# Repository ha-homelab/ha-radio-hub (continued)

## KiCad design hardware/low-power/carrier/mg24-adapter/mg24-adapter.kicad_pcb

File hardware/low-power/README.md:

# Low-power LP-P0: prototype hardware contract

<!-- MC2-CURRENT-DESIGN -->
> **Current build: [MC2 — three external antennas](../../docs/external-antennas.md).** This page retains an earlier design or evaluation for reference. Its board images, pin maps, enclosure fit and alternative BOMs are not the current MC2 build.

This is a separate design with **one S3 host and one Ethernet interface**, three dedicated radio controllers H2/MG24/ZAC93, and CC1101. Assembly, firmware for the individual radio modules and hardware testing are required. No board has been fabricated or tested, and there is no verified “3 W” result.
The [ready-module carrier](carrier/) and [integrated board](integrated/) are
separate engineering revisions; use their own verification reports and connector maps.

The current calculation gives scenarios of **2.03 / 2.82 / 4.92 W incremental AC power**. These are not measurements or a confidence interval. **3 W AC is a testable target**, not a guaranteed specification. Detailed assumptions, current reserves and calculation boundaries are in [power-budget.json](power-budget.json); the earlier architectures are compared separately in [energy-comparison.json](energy-comparison.json).

## Files and validation

- [BOM](bom.json): exact main models, quantities, `bench`/`carrier`/`both` stages and primary sources. Do not combine alternatives for different stages into a single order.
- [Pinmap](pinmap.json) and [wiring CSV](wiring.csv): 26 unique S3 GPIOs, three native UARTs and two SPI buses. The CSV defines signals; a GPIO number is not a header contact number.
- [Visual connection atlas](visual/README.md): offline interactive pin-to-pin guide, part identification sketches and printable connection sheets, with physical-pad evidence and unverified header positions distinguished.
- [Manufacturing and sales](../../docs/manufacturing.md): first articles, batch sizes, fabrication services and all three delivery formats.
- The [combined firmware](../../firmware/low-power/hub.yaml) uses the same GPIOs. Build status and software limitations are in [firmware/low-power](../../firmware/low-power/).
- [Enclosure mockup](../../mechanical/low-power/): 160×100 mm carrier reservation, 190×145×45 mm shell. The EvalPoE/DevKit development boards are not claimed to fit this enclosure.

Run from the repository root: `python3 hardware/low-power/validate.py`. This checks contracts and arithmetic, not electrical operation.

## Two assembly stages

**Bench:** external active IEEE 802.3af/at PSE → Ethernet cable → **Silvertel EvalPoE fitted with Ag97005-FL**. EvalPoE `DATA OUT` → short RJ45 patch cable → **WIZ850io**. EvalPoE isolated 5 V output → fused distribution → LD2450 and **Pololu D24V22F3**. The shared 3.3 V buck output powers S3, H2, MGM240P, ZAC93, CC1101, SC16 and BME680. There is no internal switch; one external cable supplies power.

EvalPoE compatibility with Ag97000-FL is explicitly stated on the [manufacturer's page](https://silvertel.com/ag97000/), although the PDF manual lists older models. Specify **Ag97005-FL** when ordering rather than assuming the module is included with an empty EvalPoE. Check bridge-bypass and output-filter settings against the revision of the [EvalPoE manual](https://silvertel.com/images/Eval-Board-User-Guides/POE-Eval-Board-User-Manual.pdf): the FL uses its built-in bridges, bypasses the external bridge, uses class 0 and keeps the nominal untrimmed output. Measure 5 V and polarity before connecting logic.

**Ready-module carrier (LP-C0):** distributes isolated 5 V and regulated 3.3 V,
provides a local SC16/clock/reset circuit and keyed harnesses to the controller,
radios and sensors. Its [MG24 daughterboard](carrier/mg24-adapter/) mounts the
exact MGM240PA22VNA3 and provides UART, BOOT and SWD service access.
The external EvalPoE, buck, WIZ850io and radio boards still
need separate mounting. A bare carrier does not include those modules.

**Integrated board (LP-I0):** places the bare S3/H2/MGM240P modules, W5500,
PoE magjack, Ag97005-FL, buck and support circuits on a separate PCB. ZAC93,
CC1101, radar and the external BME680 remain cable-connected. It needs its own
larger enclosure and physical bring-up; the earlier concept case is not a fit claim.

**WIZ850io does not expose PoE center taps on its SPI headers. Do not connect
Ag97005-FL inputs to those headers.** LP-C0 retains the external isolated front
end; LP-I0 uses its own specified PoE-capable magjack. A successful CAD check
is not validation of PoE isolation, Ethernet performance or radio coexistence.
Until the boards pass bring-up, EvalPoE on the bench remains the assembly path.

## Power and calculation

The selected [Ag97005-FL](https://silvertel.com/images/datasheets/Ag97000-Datasheet-low-cost-isolated-12W-Power-over-Ethernet-PoE-module-solution.pdf) is the 5 V/9 W version, 1.8 A nominal. The generic “12 W” describes the family, not this SKU. Class 0 is retained for startup/peaks; an average of 3 W AC alone does not justify selecting class 1. Use the recommended 100 µF + 100 nF + 10 µF output capacitors, accounting for parts already installed on EvalPoE. The main output-capacitance range is 47–470 µF; check additional capacitance and buck startup with an oscilloscope.

The peak **design reserve**, adding simultaneous loads, is 1.025 A at 3.3 V and 0.25 A directly at 5 V. At 85% buck efficiency and 0.15 W distribution loss, this is **5.38 W at the PD output**. It is not a guaranteed maximum for the actual modules. [D24V22F3](https://www.pololu.com/product/2857) is advertised as 2.6 A typical under specified conditions; this assembly needs a separate **1.5 A test with 5 V input** and thermal verification. Do not apply a 24 V input rating at 5 V without a curve/test. A 1.5 A slow-blow fuse on the secondary 5 V branch is an initial candidate; select the final I²t after startup testing and checking wire gauge.

Average-consumption model: `P5 = P3.3 / ηbuck + Pradar + Pwiring`, then `PAC = P5 / ηPD / ηcable / ηPSE`. The ηPD input/output boundaries are the PoE module pins; built-in bridges are already included. Low-voltage wiring is counted once. The 81.5% value is the selected FL's **peak typical** datasheet efficiency, not a guaranteed efficiency at 1.9 W. The model uses 68/76/81.5%; the two lower values are assumptions pending measurement. Add the fixed consumption of a new dedicated PSE separately; the already-running shared HA server and baseline network-infrastructure consumption are excluded.

The minimum load for maintaining PoE MPS is 70 mA at 5 V. Continuous LD2450 operation normally supplies this load, but startup and fault states must be checked; no parallel resistor for waste heat is added in advance. Required network/BLE/radar functions must remain active: disabling them does not qualify as reaching 3 W. The W5500 firmware forces 10 Mbps half-duplex; the budget deliberately retains the conservative 100 Mbps estimate without subtracting expected savings. Link stability and actual power have not yet been measured.

## S3, UARTs and the actual DevKit

The target module is **ESP32-S3-WROOM-1-N16R8**. GPIO26–37 are excluded because of flash/PSRAM, 19/20 are reserved for native USB, and 0/3/45/46 are excluded as strapping pins. GPIO38 is free. UART0 belongs to LD2450, UART1 to the MG24 TCP bridge with RTS/CTS, and UART2 to H2 OTBR. These UART numbers do not determine physical GPIOs: the GPIO matrix is used. There is no fourth native UART, so ZAC93 connects through SC16IS752.

Existing DevKits require **physical** changes before connection:

1. The S3 development board's USB–UART TX must not drive GPIO44, which receives H2 TX. Check/isolate the USB–UART connections to 43/44 and the effect of auto-reset against the actual board schematic. Selecting native USB in YAML does not disconnect these traces.
2. Similarly, on the H2 DevKit, check and isolate USB–UART TX from GPIO23, which will receive S3 data. Do not join two push-pull outputs.
3. GPIO48 must be free of the RGB LED; the official DevKitC-1 v1.1 has its LED on 38, while the earlier version uses 48. An “N16R8” label does not identify the board revision.
4. External 3.3 V and USB/5 V must not power different regulators in parallel. Disconnect the shared supply and peripherals for initial flashing; on a running bench setup, use a verified USB data-only/isolated-VBUS path. Check for back-powering and loading of an unpowered controller through UART.

The [official DevKit guide](https://docs.espressif.com/projects/esp-idf/en/v5.1.2/esp32s3/hw-reference/esp32s3/user-guide-devkitc-1.html) and [S3 datasheet](https://www.espressif.com/sites/default/files/documentation/esp32-s3-wroom-1_wroom-1u_datasheet_en.pdf) define these constraints. An unverified clone cannot be treated as a drop-in board for this pinout.

## H2 and MG24

**ESP32-H2-MINI-1-H4S**, 4 MB, is a dedicated Thread RCP, not another IP host. S3 TX43 → H2 GPIO23 RX, H2 GPIO24 TX → S3 RX44. S3 GPIO47 controls EN and GPIO48 controls BOOT/GPIO9; both outputs are open-drain, with HIGH meaning the line is released through an external pull-up. EN: 10 kΩ to 3.3 V + 1 µF to GND; BOOT: 10 kΩ to 3.3 V. Also pull H2 GPIO8 up to 3.3 V through 10 kΩ: download boot requires GPIO8=1, GPIO9=0. Hold GPIO25 low with 10 kΩ to GND; do not change eFuses. Keep EN/BOOT/GND service test points accessible. [H2 datasheet](https://www.espressif.com/sites/default/files/documentation/esp32-h2-mini-1_mini-1u_datasheet_en.pdf).

**MGM240PA22VNA3** is the selected +10 dBm MG24 variant with a built-in antenna. It requires a custom Ember NCP image with UART 115200, 8N1 and hardware RTS/CTS matching this contract: S3 TX17 → PA05/pad12 RX; PA06/pad13 TX → S3 RX18; S3 RTS16 → PB01/pad5 CTS; PB00/pad6 RTS → S3 CTS21. An [NCP and UART-XMODEM bootloader have been built](../../firmware/low-power/mg24/) for this assignment using Simplicity SDK 2025.6.3 / Zigbee 8.2.3 / EZSP 18. Generation, compilation, CRC and image checks passed; module flashing, UART/CTS, pairing and radio-network operation have not yet been tested. Factory and SLZB images are not claimed to be interchangeable.

To enter the built bootloader, expose **PA00/pad7 BOOT** with 10 kΩ to 3.3 V and a separate service jumper to GND; hold it LOW during reset. This uses no S3 GPIO. For SWD, expose PA01/pad8 SWCLK, PA02/pad9 SWDIO, RESETn/pad31, GND and 3.3 V VTref. RESETn has an internal pull-up to DVDD: only pull it to GND and release it; **do not add an external pull-up to 3.3 V**. Connect power to VDD/pad15 and all GND pins according to the [MGM240P datasheet](https://www.silabs.com/documents/public/data-sheets/mgm240p-datasheet.pdf). Verify the service-connector pinout against the selected programmer; USB-UART does not replace SWD for initial programming of a blank module.

## SC16IS752 and ZAC93

The selected part is **SC16IS752IPW,128, TSSOP28**. SPI is shared with CC1101, with separate CS pins GPIO41 and 15. IRQ pin15 → S3 GPIO42, with **1 kΩ to 3.3 V**, according to [NXP rev9.1](https://www.nxp.com/docs/en/data-sheet/SC16IS752_SC16IS762.pdf). I2C/SPI pin9 and unused SDA pin14 → GND. Supply pin8=3.3 V, pin22=GND. The current driver uses SPI mode 0 at 4 MHz; the SC16IS752 limit is 4 MHz, not the SC16IS762's 15 MHz.

Channel A: TXA/pin3 → ZAC93 header pin8 RX; ZAC93 pin10 TX → RXA/pin4. ZAC93 pin1=3.3 V, pin6/9=GND; do not connect other contacts without checking the revision. Hardware flow control is disabled; CTSA/pin2 and CTSB/pin16 → GND; RXB/pin24 is pulled up to 3.3 V through 10 kΩ; RTSA/RTSB/TXB outputs remain unconnected. The eight unused GPIOs have separate 100 kΩ resistors to GND to prevent floating inputs without shorting a future output.

Use an **ABLS-3.6864MHZ-B2-T** crystal between XTAL1/pin6 and XTAL2/pin7; prescaler 1 and divisor 2 give 115200 baud. Initial 22/33 pF C0G load capacitors come from the NXP example and require frequency/startup checks with the actual 18 pF crystal and stray capacitance. Initially keep the SPI harness no longer than 5 cm and check edges/noise with an oscilloscope; adjust driver speed and repeat testing if needed. **The firmware setting `crystal_frequency: 3686400` is mandatory.** A typical off-the-shelf 14.7456 MHz breakout is not interchangeable without configuration/driver changes.

RESET/pin5 receives the open-drain output of **TPS3808G33DBVR**, with 10 kΩ to 3.3 V; VDD/SENSE=3.3 V, CT unconnected (20 ms), and MR may use its internal pull-up or a button to GND. Install 100 nF at VDD and 1 nF at SENSE. [TI datasheet](https://www.ti.com/lit/ds/symlink/tps3808.pdf). SC16 power starts alongside the S3; software reset does not replace slow-ramp/brownout testing.

A 64-byte FIFO fills in about 5.56 ms of continuous data at 115200 8N1. The handler must service IRQ before the remaining FIFO headroom runs out; a 2048-byte software queue cannot compensate for late hardware-FIFO reads. Stress-test alongside RF TX, BLE, Ethernet and Thread. Loss/overrun must not silently turn into valid Z-Wave messages.

## RF, sensors, antennas and enclosure

CC1101: shared SPI7/8/6, CS15, GDO0→GPIO4 open-drain with 4.7 kΩ to 3.3 V, GDO2→GPIO5. This is a two-signal RF design; boards without accessible GDO2 need a separate solution. Preserve the existing RF contract/encodings when connecting to the new host. Check the clone's physical contacts against its markings, not an arbitrary photo.

LD2450 receives 5 V directly from the PD, with UART TX→S3 GPIO40 and RX←GPIO39 and common secondary GND. BME680 VIN receives 3.3 V, SDA1/SCL2, 100 kHz, address 0x77. Use the stock Adafruit pull-ups; keep the external pod away from heat and initially limit I²C to 10–20 cm. Adding sensors requires capacitance/edge margin; a free address does not imply GPIO/power headroom. BME680 gas resistance is not a direct CO₂ measurement.

Retain the stock antennas: S3 PCB, H2 PCB, built-in MGM240P, regional ZAC93 and the existing 433 MHz CC1101 antenna. Do not substitute 2.4/5.8 GHz antennas for 433 MHz. Place antennas along the carrier edges, away from metal, buck/PoE circuitry and cable bundles; apply each module's datasheet keep-out rather than a single general rule. Simultaneous BLE/Thread/Zigbee operation at 2.4 GHz requires loss/latency checks and channel selection. Individual radio certifications do not certify the combined enclosure.

The radar looks through a 1.2 mm nonmetallic wall; radome geometry and the absence of conductive fillers matter. ZAC93 limits ambient temperature around it to 0…40 °C; the S3 N16R8 has a 65 °C limit, which does not justify heating ZAC93 above 40 °C. Measure air temperature near the modules separately from buck surface temperature. The low-power drawings retain **unmeasured** envelopes for the existing ZAC93/CC1101, wires and connectors.

## Before releasing a hardware revision

1. Check actual modules/connectors, DevKit UART isolation, GDO2, GPIO48 and the 3.3 V supply. Do not connect unisolated interfaces with two active drivers.
2. Assemble on the bench with EvalPoE; check rails, MPS, cold start, load transients and thermal performance. Record AC and DC separately.
3. Flash H2 and MG24, check UART/CTS and SC16 without RF load, then exercise all functions together, including long runs and recovery from power/Ethernet loss.
4. Review the selected PCB revision and its verification report before first-article fabrication. Resolve electrical, isolation, return-path, RF keep-out and mechanical findings, then run DFM and bench validation. The earlier enclosure mockup is not proof of fit for either complete assembly.

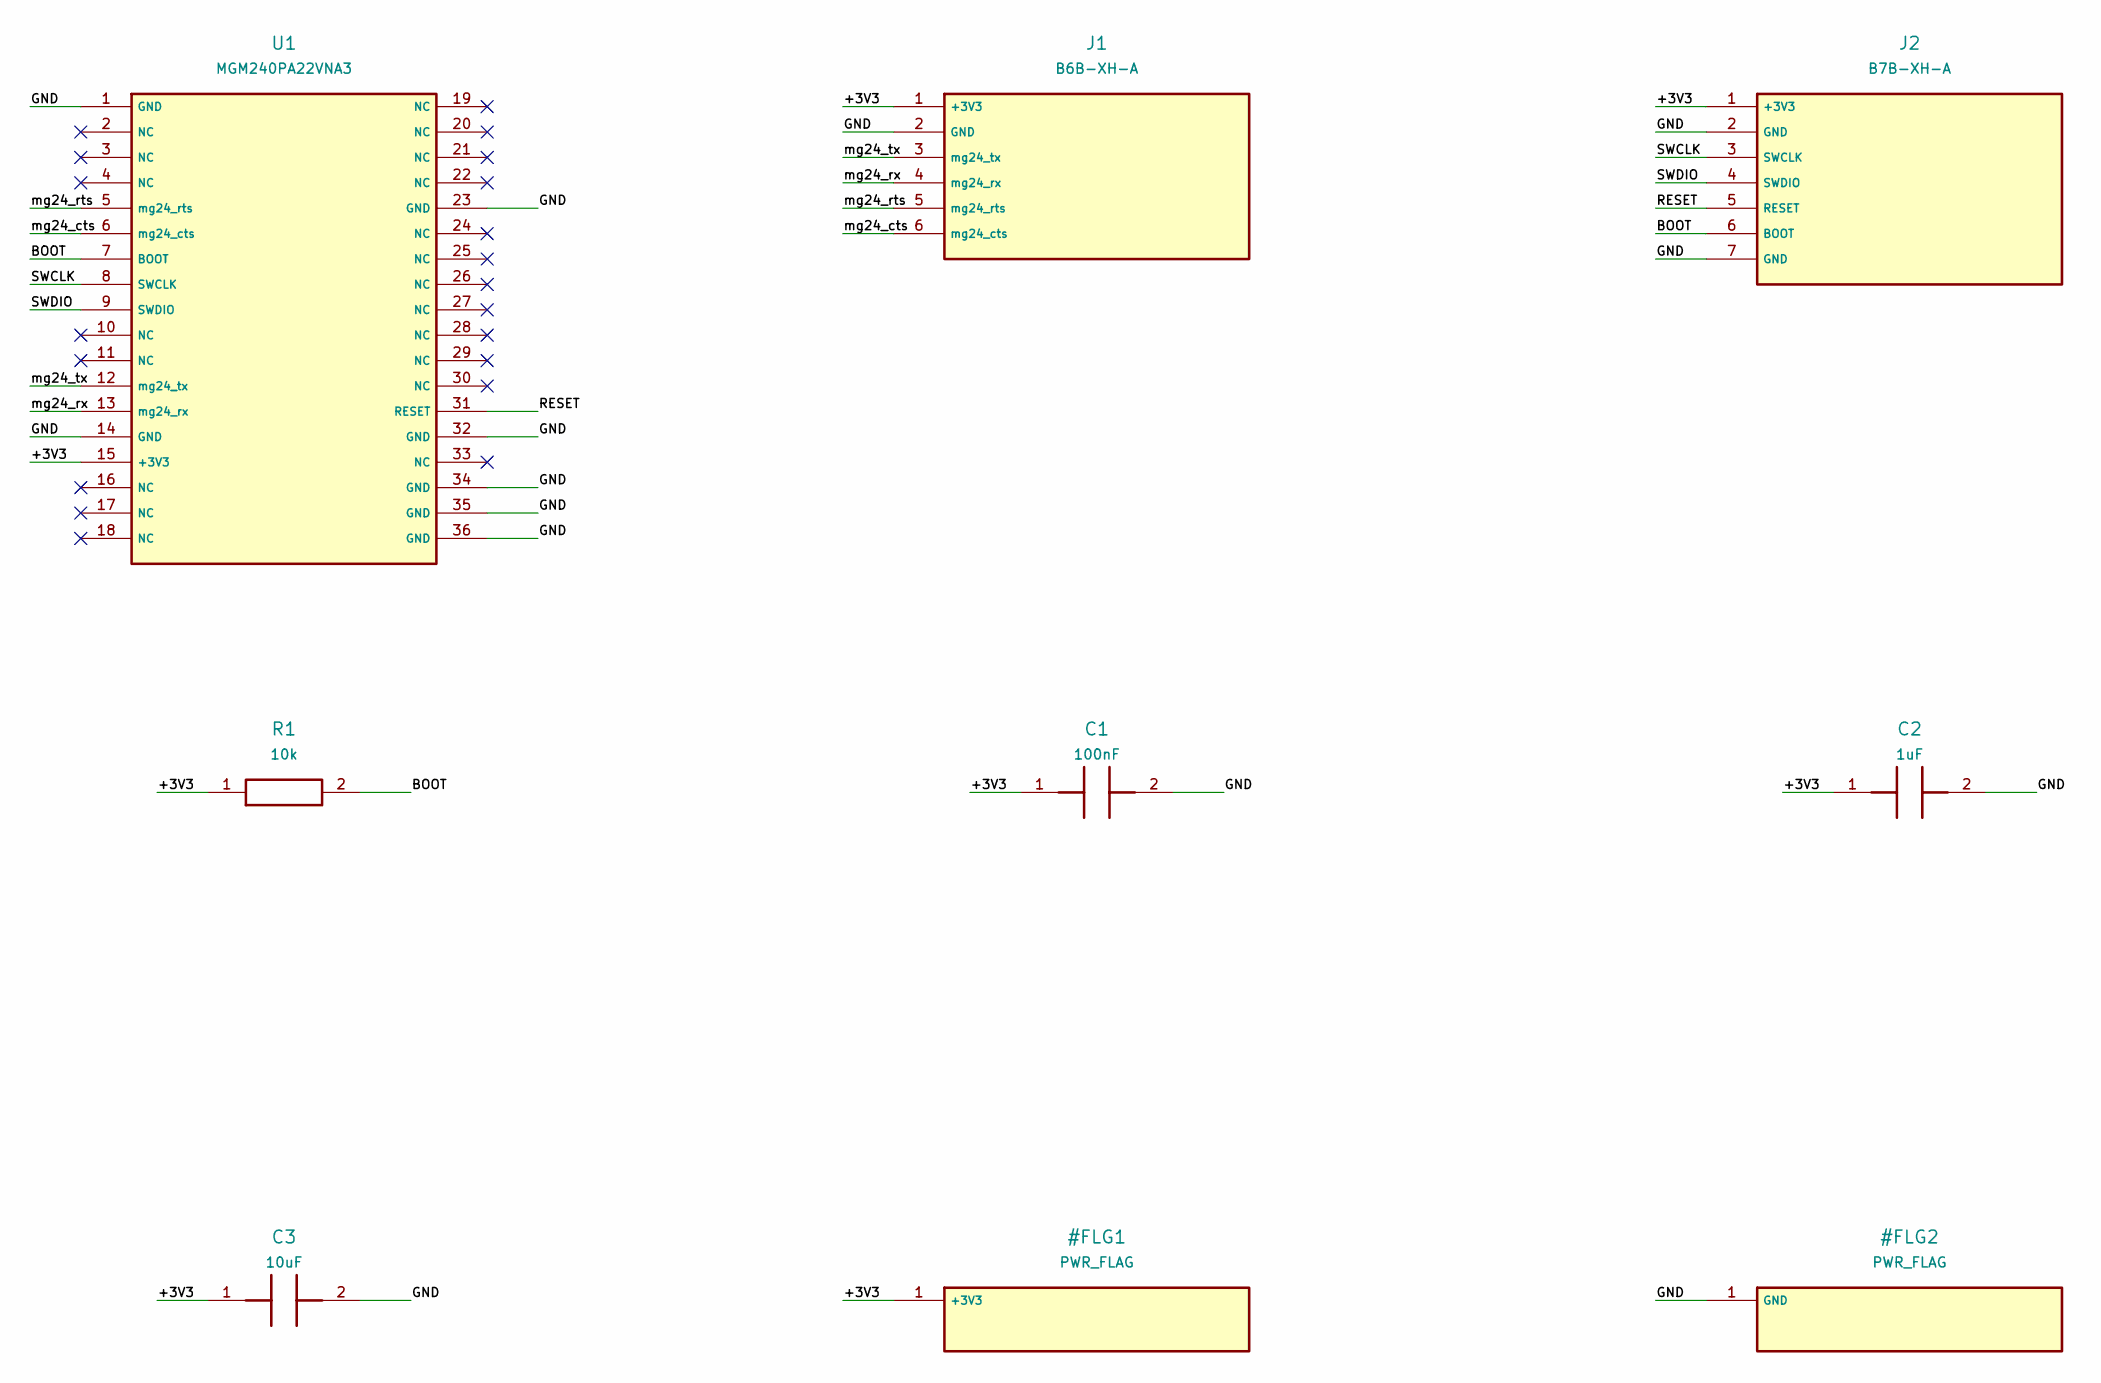
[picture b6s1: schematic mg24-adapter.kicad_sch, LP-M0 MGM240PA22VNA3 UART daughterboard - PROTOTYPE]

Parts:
C1: 100nF; C_0805_2012Metric
C2: 1uF; C_0805_2012Metric
C3: 10uF; C_1206_3216Metric
J1: B6B-XH-A; JST_XH_B6B-XH-A_1x06_P2.50mm_Vertical
J2: B7B-XH-A; JST_XH_B7B-XH-A_1x07_P2.50mm_Vertical
R1: 10k; R_0805_2012Metric
U1: MGM240PA22VNA3; MGM240P

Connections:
/+3V3: C1.1, C2.1, C3.1, J1.1 (+3V3), J2.1 (+3V3), R1.1, U1.15 (+3V3)
/BOOT: J2.6 (BOOT), R1.2, U1.7 (BOOT)
/GND: C1.2, C2.2, C3.2, J1.2 (GND), J2.2 (GND), J2.7 (GND), U1.1 (GND), U1.14 (GND), U1.23 (GND), U1.32 (GND), U1.34 (GND), U1.35 (GND), U1.36 (GND)
/RESET: J2.5 (RESET), U1.31 (RESET)
/SWCLK: J2.3 (SWCLK), U1.8 (SWCLK)
/SWDIO: J2.4 (SWDIO), U1.9 (SWDIO)
/mg24_cts: J1.6 (mg24_cts), U1.6 (mg24_cts)
/mg24_rts: J1.5 (mg24_rts), U1.5 (mg24_rts)
/mg24_rx: J1.4 (mg24_rx), U1.13 (mg24_rx)
/mg24_tx: J1.3 (mg24_tx), U1.12 (mg24_tx)

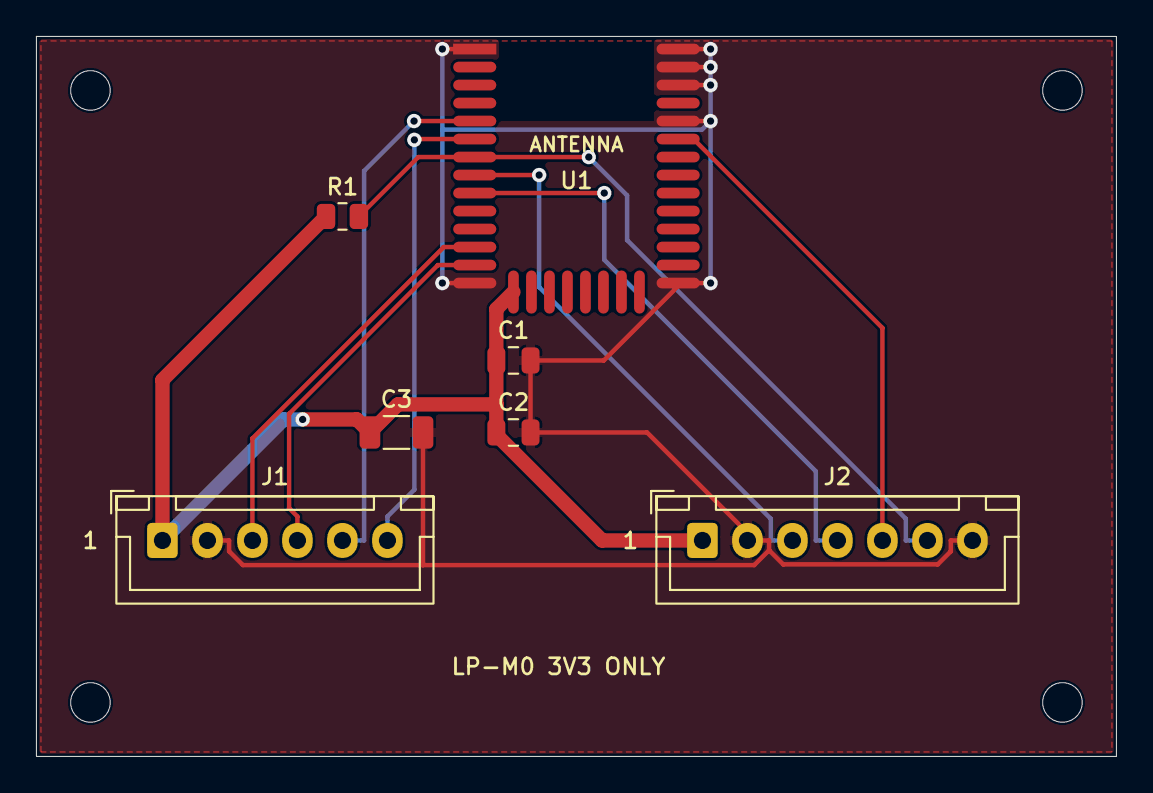
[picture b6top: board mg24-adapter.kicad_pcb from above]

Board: 2 copper layers, 60.0 x 40.0 mm, 11 parts (0 on the bottom side), 10 nets.

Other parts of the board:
H1, H2, H3, H4: M2 NPTH

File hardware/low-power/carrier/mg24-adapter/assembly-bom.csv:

Reference,Quantity,Manufacturer part / value,Footprint,Note,Source
U1,1,MGM240PA22VNA3,Carrier:MGM240P,Exact PA22VNA3 firmware target; all GND pads direct to plane; RFOUT33 intentionally NC,https://www.silabs.com/documents/public/data-sheets/mgm240p-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
J1,1,B6B-XH-A,Carrier:JST_XH_B6B-XH-A_1x06_P2.50mm_Vertical,To carrier J6,https://www.jst-mfg.com/product/pdf/eng/eXH.pdf
J2,1,B7B-XH-A,Carrier:JST_XH_B7B-XH-A_1x07_P2.50mm_Vertical,SWD / reset / boot service,https://www.jst-mfg.com/product/pdf/eng/eXH.pdf
R1,1,10k,Carrier:R_0805_2012Metric,"1%, 0.125W, 0805",
C1,1,100nF,Carrier:C_0805_2012Metric,"10V X7R, 0805, close to VDD15",
C2,1,1uF,Carrier:C_0805_2012Metric,"10V X7R, 0805",
C3,1,10uF,Carrier:C_1206_3216Metric,"10V X7R, 1206; account for DC bias",

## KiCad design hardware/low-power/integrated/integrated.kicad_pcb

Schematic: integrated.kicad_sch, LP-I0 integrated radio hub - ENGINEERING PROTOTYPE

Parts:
C1: 22pF; C_0805_2012Metric
C2: 33pF; C_0805_2012Metric
C3, C6, C9, C13, C15, C17, C18, C19, C20, C21, C22, C23, C24, C25, C27, C42: 100nF; C_0805_2012Metric
C4, C7, C10, C26, C28, C43: 10uF; C_1206_3216Metric
C5, C8, C12: 1uF; C_0805_2012Metric
C11: 100nF; C_0603_1608Metric
C14: 1nF; C_0805_2012Metric
C16, C39, C40, C41: 22uF; C_1206_3216Metric
C29, C36: 10nF; C_0805_2012Metric
C30: 4.7uF; C_0805_2012Metric
C31, C32: 18pF; C_0805_2012Metric
C33: 22nF; C_0805_2012Metric
C34, C35: 6.8nF; C_0805_2012Metric
C37, C38: 10nF 100V; C_1206_3216Metric
C50: 1nF 2kV; C_Disc_D7.5mm_W5.0mm_P7.50mm
D1, D2: SMBJ58CA; D_SMB
F1: 044901.5MR; Littelfuse_449
FB1: BLM21PG121SN1D; L_0805_2012Metric
J1: 0813-1X1T-57-F; Bel_0813_1X1T_57_F
J2: TYPE-C-31-M-12; USB_C_Receptacle_HRO_TYPE-C-31-M-12
J3: B8B-XH-A; JST_XH_B8B-XH-A_1x08_P2.50mm_Vertical
J4: B5B-XH-A; JST_XH_B5B-XH-A_1x05_P2.50mm_Vertical
J5: B4B-XH-A; JST_XH_B4B-XH-A_1x04_P2.50mm_Vertical
J6: BM04B-SRSS-TB; JST_SH_BM04B-SRSS-TB_1x04-1MP_P1.00mm_Vertical
J7, J8: B6B-XH-A; JST_XH_B6B-XH-A_1x06_P2.50mm_Vertical
R1: 1k; R_0805_2012Metric
R2, R3, R4, R6, R7, R8, R9, R10, R11, R12, R13, R14, R15, R16: 10k; R_0805_2012Metric
R5: 4.7k; R_0805_2012Metric
R17, R18: 5.1k; R_0805_2012Metric
R19, R20: 22; R_0805_2012Metric
R21, R22, R23, R24, R25, R26, R27, R28: 100k; R_0805_2012Metric
R29: 12.4k; R_0805_2012Metric
R30: 1M; R_0805_2012Metric
R31, R32, R34, R35: 49.9; R_0805_2012Metric
R33: 10; R_0805_2012Metric
SW1, SW2, SW3, SW4: SW_PUSH; SW_SPST_TL3342
U1: ESP32-S3-WROOM-1-N16R8; ESP32-S3-WROOM-1
U2: ESP32-H2-MINI-1-H4S; ESP32-H2-MINI-1
U3: MGM240PA22VNA3; MGM240P
U4: W5500; LQFP-48_7x7mm_P0.5mm
U5: NXP SC16IS752IPW,128 / TSSOP28; TSSOP-28_4.4x9.7mm_P0.65mm
U6: TI TPS3808G33DBVR / SOT-23-6; SOT-23-6
U7: Ag97005-FL; Ag97000_FL
U8: D24V22F3
U9: USBLC6-2SC6; SOT-23-6
Y1: ABLS-3.6864MHZ-B2-T; Crystal_SMD_HC49-SD
Y2: ABM8-25.000MHZ-B2-T; Crystal_SMD_3225-4Pin_3.2x2.5mm

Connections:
3v3: C3.1 (3v3), C4.1 (3v3), C6.1 (3v3), C7.1 (3v3), C9.1 (3v3), C10.1 (3v3), C11.1 (3v3), C12.1 (3v3), C13.1 (3v3), C14.1 (3v3), C16.1 (3v3), C17.1 (3v3), C18.1 (3v3), C27.1 (3v3), C28.1 (3v3), FB1.1 (3v3), J3.1 (3v3), J4.1 (3v3), J6.2 (3v3), J7.1 (3v3), J8.1 (3v3), R1.2 (3v3), R2.2 (3v3), R3.2 (3v3), R4.2 (3v3), R5.2 (3v3), R6.2 (3v3), R7.2 (3v3), R8.2 (3v3), R9.2 (3v3), R11.2 (3v3), R12.2 (3v3), R13.2 (3v3), R14.2 (3v3), R15.2 (3v3), R16.2 (3v3), U1.2 (3v3), U2.3 (3v3), U3.15 (3v3), U4.28 (3v3), U5.8 (3v3), U6.5 (3v3), U6.6 (3v3), U8.VOUT (3v3)
3v3_analog: C20.1 (3v3_analog), C21.1 (3v3_analog), C22.1 (3v3_analog), C23.1 (3v3_analog), C24.1 (3v3_analog), C25.1 (3v3_analog), C26.1 (3v3_analog), FB1.2 (3v3_analog), R31.2 (3v3_analog), R32.2 (3v3_analog), R33.2 (3v3_analog), U4.4 (3v3_analog), U4.8 (3v3_analog), U4.11 (3v3_analog), U4.15 (3v3_analog), U4.17 (3v3_analog), U4.21 (3v3_analog)
5v_fused: C19.1 (5v_fused), F1.2 (5v_fused), J5.1 (5v_fused), U8.VIN (5v_fused)
5v_pd: C39.1 (5v_pd), C40.1 (5v_pd), C41.1 (5v_pd), C42.1 (5v_pd), C43.1 (5v_pd), F1.1 (5v_pd), U7.8 (5v_pd)
POE_12: C37.1 (POE_12), D1.1 (POE_12), J1.5 (POE_12), U7.1 (POE_12)
POE_36: C37.2 (POE_36), D1.2 (POE_36), J1.10 (POE_36), U7.2 (POE_36)
POE_45: C38.1 (POE_45), D2.1 (POE_45), J1.6 (POE_45), U7.3 (POE_45)
POE_78: C38.2 (POE_78), D2.2 (POE_78), J1.11 (POE_78), U7.4 (POE_78)
bme680_scl: J6.4 (bme680_scl), U1.38 (bme680_scl)
bme680_sda: J6.3 (bme680_sda), U1.39 (bme680_sda)
cc1101_cs: J3.6 (cc1101_cs), R6.1 (cc1101_cs), U1.8 (cc1101_cs)
cc1101_gdo0_tx: J3.7 (cc1101_gdo0_tx), R5.1 (cc1101_gdo0_tx), U1.4 (cc1101_gdo0_tx)
cc1101_gdo2_rx: J3.8 (cc1101_gdo2_rx), U1.5 (cc1101_gdo2_rx)
chassis: C50.1 (chassis), J1.S1 (chassis), J1.S2 (chassis)
eth_1v2: C29.1 (eth_1v2), U4.22 (eth_1v2)
eth_exres: R29.1 (eth_exres), U4.10 (eth_exres)
eth_pmode: R16.1 (eth_pmode), U4.43 (eth_pmode), U4.44 (eth_pmode), U4.45 (eth_pmode)
eth_rxn: C35.1 (eth_rxn), R35.1 (eth_rxn), U4.5 (eth_rxn)
eth_rxp: C34.1 (eth_rxp), R34.1 (eth_rxp), U4.6 (eth_rxp)
eth_rxterm: C36.1 (eth_rxterm), R34.2 (eth_rxterm), R35.2 (eth_rxterm)
eth_tocap: C30.1 (eth_tocap), U4.20 (eth_tocap)
eth_txn: J1.9 (eth_txn), R32.1 (eth_txn), U4.1 (eth_txn)
eth_txp: J1.2 (eth_txp), R31.1 (eth_txp), U4.2 (eth_txp)
eth_xi: C31.1 (eth_xi), R30.1 (eth_xi), U4.30 (eth_xi), Y2.1 (eth_xi)
eth_xo: C32.1 (eth_xo), R30.2 (eth_xo), U4.31 (eth_xo), Y2.3 (eth_xo)
gnd: C1.2 (gnd), C2.2 (gnd), C3.2 (gnd), C4.2 (gnd), C5.2 (gnd), C6.2 (gnd), C7.2 (gnd), C8.2 (gnd), C9.2 (gnd), C10.2 (gnd), C11.2 (gnd), C12.2 (gnd), C13.2 (gnd), C14.2 (gnd), C15.2 (gnd), C16.2 (gnd), C17.2 (gnd), C18.2 (gnd), C19.2 (gnd), C20.2 (gnd), C21.2 (gnd), C22.2 (gnd), C23.2 (gnd), C24.2 (gnd), C25.2 (gnd), C26.2 (gnd), C27.2 (gnd), C28.2 (gnd), C29.2 (gnd), C30.2 (gnd), C31.2 (gnd), C32.2 (gnd), C33.2 (gnd), C36.2 (gnd), C39.2 (gnd), C40.2 (gnd), C41.2 (gnd), C42.2 (gnd), C43.2 (gnd), C50.2 (gnd), J2.A1 (gnd), J2.A12 (gnd), J2.B1 (gnd), J2.B12 (gnd), J2.SH (gnd), J3.2 (gnd), J4.2 (gnd), J4.5 (gnd), J5.2 (gnd), J6.1 (gnd), J7.2 (gnd), J8.2 (gnd), R10.2 (gnd), R17.2 (gnd), R18.2 (gnd), R21.2 (gnd), R22.2 (gnd), R23.2 (gnd), R24.2 (gnd), R25.2 (gnd), R26.2 (gnd), R27.2 (gnd), R28.2 (gnd), R29.2 (gnd), SW1.2 (gnd), SW2.2 (gnd), SW3.2 (gnd), SW4.2 (gnd), U1.1 (gnd), U1.40 (gnd), U1.41 (gnd), U2.1 (gnd), U2.2 (gnd), U2.11 (gnd), U2.14 (gnd), U2.36 (gnd), U2.37 (gnd), U2.38 (gnd), U2.39 (gnd), U2.40 (gnd), U2.41 (gnd), U2.42 (gnd), U2.43 (gnd), U2.44 (gnd), U2.45 (gnd), U2.46 (gnd), U2.47 (gnd), U2.48 (gnd), U2.49 (gnd), U2.50 (gnd), U2.51 (gnd), U2.52 (gnd), U2.53 (gnd), U3.1 (gnd), U3.14 (gnd), U3.23 (gnd), U3.32 (gnd), U3.34 (gnd), U3.35 (gnd), U3.36 (gnd), U4.3 (gnd), U4.9 (gnd), U4.14 (gnd), U4.16 (gnd), U4.19 (gnd), U4.23 (gnd), U4.29 (gnd), U4.48 (gnd), U5.2 (gnd), U5.9 (gnd), U5.14 (gnd), U5.16 (gnd), U5.22 (gnd), U6.2 (gnd), U7.7 (gnd), U8.GND (gnd), U8.GND2 (gnd), U9.2 (gnd), Y2.2 (gnd), Y2.4 (gnd)
h2_boot: J8.6 (h2_boot), R8.1 (h2_boot), U1.25 (h2_boot), U2.23 (h2_boot)
h2_gpio8: R9.1 (h2_gpio8), U2.22 (h2_gpio8)
h2_gpio25: R10.1 (h2_gpio25), U2.25 (h2_gpio25)
h2_reset: C8.1 (h2_reset), J8.5 (h2_reset), R7.1 (h2_reset), U1.24 (h2_reset), U2.8 (h2_reset)
h2_rx: J8.3 (h2_rx), U1.36 (h2_rx), U2.31 (h2_rx)
h2_tx: J8.4 (h2_tx), U1.37 (h2_tx), U2.30 (h2_tx)
ld2450_rx: J5.3 (ld2450_rx), U1.33 (ld2450_rx)
ld2450_tx: J5.4 (ld2450_tx), U1.32 (ld2450_tx)
mag_ct: C33.1 (mag_ct), J1.7 (mag_ct), R33.1 (mag_ct)
mag_rxn: C35.2 (mag_rxn), J1.8 (mag_rxn)
mag_rxp: C34.2 (mag_rxp), J1.1 (mag_rxp)
mg24_boot: J7.6 (mg24_boot), R11.1 (mg24_boot), SW4.1 (mg24_boot), U3.7 (mg24_boot)
mg24_cts: U1.23 (mg24_cts), U3.6 (mg24_cts)
mg24_reset: J7.5 (mg24_reset), SW3.1 (mg24_reset), U3.31 (mg24_reset)
mg24_rts: U1.9 (mg24_rts), U3.5 (mg24_rts)
mg24_rx: U1.11 (mg24_rx), U3.13 (mg24_rx)
mg24_swclk: J7.3 (mg24_swclk), U3.8 (mg24_swclk)
mg24_swdio: J7.4 (mg24_swdio), U3.9 (mg24_swdio)
mg24_tx: U1.10 (mg24_tx), U3.12 (mg24_tx)
s3_boot: R13.1 (s3_boot), SW2.1 (s3_boot), U1.27 (s3_boot)
s3_en: C5.1 (s3_en), R12.1 (s3_en), SW1.1 (s3_en), U1.3 (s3_en)
sc16_cs: R3.1 (sc16_cs), U1.34 (sc16_cs), U5.10 (sc16_cs)
sc16_gpio0: R21.1 (sc16_gpio0), U5.18 (sc16_gpio0)
sc16_gpio1: R22.1 (sc16_gpio1), U5.19 (sc16_gpio1)
sc16_gpio2: R23.1 (sc16_gpio2), U5.20 (sc16_gpio2)
sc16_gpio3: R24.1 (sc16_gpio3), U5.21 (sc16_gpio3)
sc16_gpio4: R25.1 (sc16_gpio4), U5.25 (sc16_gpio4)
sc16_gpio5: R26.1 (sc16_gpio5), U5.26 (sc16_gpio5)
sc16_gpio6: R27.1 (sc16_gpio6), U5.27 (sc16_gpio6)
sc16_gpio7: R28.1 (sc16_gpio7), U5.28 (sc16_gpio7)
sc16_irq: R1.1 (sc16_irq), U1.35 (sc16_irq), U5.15 (sc16_irq)
sc16_reset: R2.1 (sc16_reset), U5.5 (sc16_reset), U6.1 (sc16_reset)
sc16_rxb: R4.1 (sc16_rxb), U5.24 (sc16_rxb)
sc16_xtal1: C1.1 (sc16_xtal1), U5.6 (sc16_xtal1), Y1.1 (sc16_xtal1)
sc16_xtal2: C2.1 (sc16_xtal2), U5.7 (sc16_xtal2), Y1.2 (sc16_xtal2)
shared_spi_miso: J3.5 (shared_spi_miso), U1.6 (shared_spi_miso), U5.12 (shared_spi_miso)
shared_spi_mosi: J3.4 (shared_spi_mosi), U1.12 (shared_spi_mosi), U5.11 (shared_spi_mosi)
shared_spi_sclk: J3.3 (shared_spi_sclk), U1.7 (shared_spi_sclk), U5.13 (shared_spi_sclk)
usb_cc1: J2.A5 (usb_cc1), R17.1 (usb_cc1)
usb_cc2: J2.B5 (usb_cc2), R18.1 (usb_cc2)
usb_dm: R19.2 (usb_dm), U1.13 (usb_dm)
usb_dm_port: J2.A7 (usb_dm_port), J2.B7 (usb_dm_port), R19.1 (usb_dm_port), U9.1 (usb_dm_port), U9.6 (usb_dm_port)
usb_dp: R20.2 (usb_dp), U1.14 (usb_dp)
usb_dp_port: J2.A6 (usb_dp_port), J2.B6 (usb_dp_port), R20.1 (usb_dp_port), U9.3 (usb_dp_port), U9.4 (usb_dp_port)
usb_vbus: C15.1 (usb_vbus), J2.A4 (usb_vbus), J2.A9 (usb_vbus), J2.B4 (usb_vbus), J2.B9 (usb_vbus), U9.5 (usb_vbus)
w5500_cs: R14.1 (w5500_cs), U1.22 (w5500_cs), U4.32 (w5500_cs)
w5500_irq: U1.18 (w5500_irq), U4.36 (w5500_irq)
w5500_miso: U1.20 (w5500_miso), U4.34 (w5500_miso)
w5500_mosi: U1.19 (w5500_mosi), U4.35 (w5500_mosi)
w5500_reset: R15.1 (w5500_reset), U1.17 (w5500_reset), U4.37 (w5500_reset)
w5500_sclk: U1.21 (w5500_sclk), U4.33 (w5500_sclk)
zwave_rx: J4.4 (zwave_rx), U5.4 (zwave_rx)
zwave_tx: J4.3 (zwave_tx), U5.3 (zwave_tx)

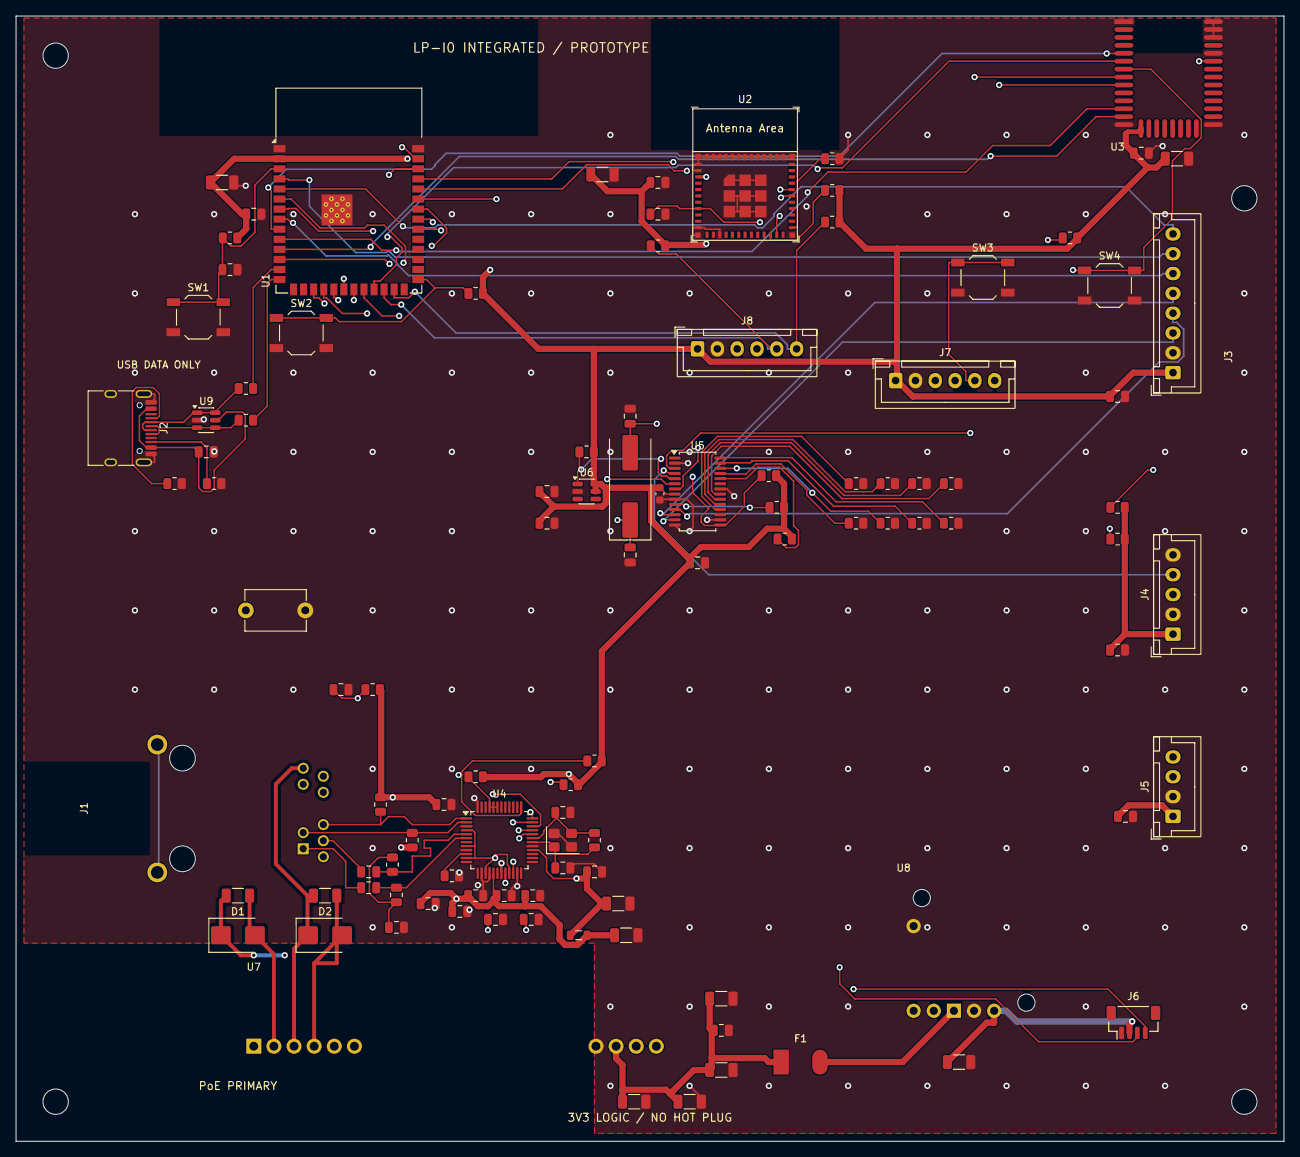
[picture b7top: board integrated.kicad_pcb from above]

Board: 4 copper layers, 160.0 x 142.0 mm, 110 parts (0 on the bottom side), 79 nets.

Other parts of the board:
H1, H2, H3, H4: M3 NPTH; MountingHole_3.2mm_M3

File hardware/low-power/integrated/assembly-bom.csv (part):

Reference,Quantity,Manufacturer part / value,Footprint,Note,Source
U1,1,ESP32-S3-WROOM-1-N16R8,Hub:ESP32-S3-WROOM-1,"Module pad numbers, not development-board header positions.","{'url': 'https://www.espressif.com/sites/default/files/documentation/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, 'revision': '1.8', 'section': 'Table 3-1, pages 11-12', 'checked_date': '2026-10-17'}"
U2,1,ESP32-H2-MINI-1-H4S,Hub:ESP32-H2-MINI-1,"Module pad numbers, not development-board header positions.","{'url': 'https://www.espressif.com/sites/default/files/documentation/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, 'revision': '1.6', 'section': 'Table 3, page 10', 'checked_date': '2026-10-17'}"
U3,1,MGM240PA22VNA3,Hub:MGM240P,"Module pad numbers, not development-board header positions.","{'url': 'https://www.silabs.com/documents/public/data-sheets/mgm240p-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, 'revision': '1.4', 'section': '6.1, Table 6.1', 'checked_date': '2026-10-17', 'method': 'Manufacturer PDF indexed pin table; direct PDF download unavailable during this review.'}"
U5,1,"NXP SC16IS752IPW,128 / TSSOP28",Hub:TSSOP-28_4.4x9.7mm_P0.65mm,"Module pad numbers, not development-board header positions.","{'url': 'https://www.nxp.com/docs/en/data-sheet/SC16IS752_SC16IS762.pdf', 'revision': '9.1', 'section': 'Table 2, TSSOP28 column only', 'checked_date': '2026-10-17'}"
U6,1,TI TPS3808G33DBVR / SOT-23-6,Hub:SOT-23-6,"Module pad numbers, not development-board header positions.",
U7,1,Ag97005-FL,Hub:Ag97000_FL,Bare isolated PoE module installed on this PCB; not the separate EvalPoE bench board.,"{'url': 'https://silvertel.com/images/datasheets/Ag97000-Datasheet-lo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, 'revision': '2.0', 'section': 'Table 3, Ag97000-FL, page 5', 'checked_date': '2026-10-17'}"
U8,1,D24V22F3,Hub:D24V22F3,Only regulator feeding 3V3. 1.5A at 5V input bench gate; soldered headers.,https://www.pololu.com/file/0J1031/d24v22fx-step-down-voltag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
U4,1,W5500,Hub:LQFP-48_7x7mm_P0.5mm,25MHz crystal; common-CT magnetics with RX AC coupling; hardware PMODE111; firmware selects10M.,https://docs.wiznet.io/img/products/w5500/w5500_sch_v110_use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
J1,1,0813-1X1T-57-F,Hub:Bel_0813_1X1T_57_F,"PoE-capable magjack. PHY-side common CT. Four cable-side power taps, internal bridge in U7.",https://www.belfuse.com/media/drawings/products/magjack%20IC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
J3,1,B8B-XH-A,Hub:JST_XH_B8B-XH-A_1x08_P2.50mm_Vertical,CC1101 remote RF module,https://www.jst-mfg.com/product/pdf/eng/eXH.pdf
J4,1,B5B-XH-A,Hub:JST_XH_B5B-XH-A_1x05_P2.50mm_Vertical,ZAC93 remote module,https://www.jst-mfg.com/product/pdf/eng/eXH.pdf
J5,1,B4B-XH-A,Hub:JST_XH_B4B-XH-A_1x04_P2.50mm_Vertical,LD2450 remote radar,https://www.jst-mfg.com/product/pdf/eng/eXH.pdf
J6,1,BM04B-SRSS-TB,Hub:JST_SH_BM04B-SRSS-TB_1x04-1MP_P1.00mm_Vertical,Standard QT order; breakout pullups only; short external ambient sensor cable.,https://www.jst-mfg.com/product/pdf/eng/eSH.pdf
J7,1,B6B-XH-A,Hub:JST_XH_B6B-XH-A_1x06_P2.50mm_Vertical,MG24 service SWD/boot,https://www.jst-mfg.com/product/pdf/eng/eXH.pdf
J8,1,B6B-XH-A,Hub:JST_XH_B6B-XH-A_1x06_P2.50mm_Vertical,H2 service UART/boot,https://www.jst-mfg.com/product/pdf/eng/eXH.pdf
J2,1,TYPE-C-31-M-12,Hub:USB_C_Receptacle_HRO_TYPE-C-31-M-12,Self-powered USB service only. VBUS feeds ESD reference; never tied to PoE5V.,https://www.hroelec.com/UploadFiles/2017/04/TYPE-C-31-M-12.pdf
U9,1,USBLC6-2SC6,Hub:SOT-23-6,Low-capacitance ESD near USB; VBUS not board supply.,https://www.st.com/resource/en/datasheet/usblc6-2.pdf
Y1,1,ABLS-3.6864MHZ-B2-T,Hub:Crystal_SMD_HC49-SD,18pF load; verify measured frequency and drive.,"{'url': 'https://www.nxp.com/docs/en/data-sheet/SC16IS752_SC16IS762.pdf', 'revision': '9.1', 'section': 'Table 2, TSSOP28 column only', 'checked_date': '2026-10-17'}"
C1,1,22pF,Hub:C_0805_2012Metric,"C0G,50V",
C2,1,33pF,Hub:C_0805_2012Metric,"C0G,50V",
R1,1,1k,Hub:R_0805_2012Metric,"1%,0805,0.125W",
R2,1,10k,Hub:R_0805_2012Metric,"1%,0805,0.125W",
R3,1,10k,Hub:R_0805_2012Metric,"1%,0805,0.125W",
R4,1,10k,Hub:R_0805_2012Metric,"1%,0805,0.125W",
R5,1,4.7k,Hub:R_0805_2012Metric,"1%,0805,0.125W",
R6,1,10k,Hub:R_0805_2012Metric,"1%,0805,0.125W",
R7,1,10k,Hub:R_0805_2012Metric,"1%,0805,0.125W",
R8,1,10k,Hub:R_0805_2012Metric,"1%,0805,0.125W",
R9,1,10k,Hub:R_0805_2012Metric,"1%,0805,0.125W",
R10,1,10k,Hub:R_0805_2012Metric,"1%,0805,0.125W",
R11,1,10k,Hub:R_0805_2012Metric,"1%,0805,0.125W",
R12,1,10k,Hub:R_0805_2012Metric,"1%,0805,0.125W",
R13,1,10k,Hub:R_0805_2012Metric,"1%,0805,0.125W",
R14,1,10k,Hub:R_0805_2012Metric,"1%,0805,0.125W",
R15,1,10k,Hub:R_0805_2012Metric,"1%,0805,0.125W",
R16,1,10k,Hub:R_0805_2012Metric,"1%,0805,0.125W",
R17,1,5.1k,Hub:R_0805_2012Metric,"1%,0805,0.125W",
R18,1,5.1k,Hub:R_0805_2012Metric,"1%,0805,0.125W",
R19,1,22,Hub:R_0805_2012Metric,"1%,0805,0.125W",
R20,1,22,Hub:R_0805_2012Metric,"1%,0805,0.125W",
R21,1,100k,Hub:R_0805_2012Metric,"1%,0805,0.125W",
R22,1,100k,Hub:R_0805_2012Metric,"1%,0805,0.125W",
R23,1,100k,Hub:R_0805_2012Metric,"1%,0805,0.125W",
R24,1,100k,Hub:R_0805_2012Metric,"1%,0805,0.125W",
R25,1,100k,Hub:R_0805_2012Metric,"1%,0805,0.125W",
R26,1,100k,Hub:R_0805_2012Metric,"1%,0805,0.125W",
R27,1,100k,Hub:R_0805_2012Metric,"1%,0805,0.125W",
R28,1,100k,Hub:R_0805_2012Metric,"1%,0805,0.125W",
C3,1,100nF,Hub:C_0805_2012Metric,"X7R,16V; evaluate DC-bias effective capacitance",
C4,1,10uF,Hub:C_1206_3216Metric,"X7R,16V; evaluate DC-bias effective capacitance",
C5,1,1uF,Hub:C_0805_2012Metric,"X7R,16V; evaluate DC-bias effective capacitance",
C6,1,100nF,Hub:C_0805_2012Metric,"X7R,16V; evaluate DC-bias effective capacitance",
C7,1,10uF,Hub:C_1206_3216Metric,"X7R,16V; evaluate DC-bias effective capacitance",
C8,1,1uF,Hub:C_0805_2012Metric,"X7R,16V; evaluate DC-bias effective capacitance",
C9,1,100nF,Hub:C_0805_2012Metric,"X7R,16V; evaluate DC-bias effective capacitance",
C10,1,10uF,Hub:C_1206_3216Metric,"X7R,16V; evaluate DC-bias effective capacitance",
C11,1,100nF,Hub:C_0603_1608Metric,"X7R,16V; evaluate DC-bias effective capacitance",
C12,1,1uF,Hub:C_0805_2012Metric,"X7R,16V; evaluate DC-bias effective capacitance",
C13,1,100nF,Hub:C_0805_2012Metric,"X7R,16V; evaluate DC-bias effective capacitance",
C14,1,1nF,Hub:C_0805_2012Metric,"X7R,16V; evaluate DC-bias effective capacitance",
C15,1,100nF,Hub:C_0805_2012Metric,"X7R,16V; evaluate DC-bias effective capacitance",
C16,1,22uF,Hub:C_1206_3216Metric,"X7R,16V; evaluate DC-bias effective capacitance",
C17,1,100nF,Hub:C_0805_2012Metric,"X7R,16V; evaluate DC-bias effective capacitance",
C18,1,100nF,Hub:C_0805_2012Metric,"X7R,16V; evaluate DC-bias effective capacitance",
C19,1,100nF,Hub:C_0805_2012Metric,"X7R,16V; evaluate DC-bias effective capacitance",
FB1,1,BLM21PG121SN1D,Hub:L_0805_2012Metric,"120ohm at100MHz, low DCR ferrite; local analog supply filter.",
C20,1,100nF,Hub:C_0805_2012Metric,"X7R,16V; evaluate DC-bias effective capacitance",
C21,1,100nF,Hub:C_0805_2012Metric,"X7R,16V; evaluate DC-bias effective capacitance",
C22,1,100nF,Hub:C_0805_2012Metric,"X7R,16V; evaluate DC-bias effective capacitance",
C23,1,100nF,Hub:C_0805_2012Metric,"X7R,16V; evaluate DC-bias effective capacitance",
C24,1,100nF,Hub:C_0805_2012Metric,"X7R,16V; evaluate DC-bias effective capacitance",
C25,1,100nF,Hub:C_0805_2012Metric,"X7R,16V; evaluate DC-bias effective capacitance",
C26,1,10uF,Hub:C_1206_3216Metric,"X7R,16V; evaluate DC-bias effective capacitance",
C27,1,100nF,Hub:C_0805_2012Metric,"X7R,16V; evaluate DC-bias effective capacitance",
C28,1,10uF,Hub:C_1206_3216Metric,"X7R,16V; evaluate DC-bias effective capacitance",
R29,1,12.4k,Hub:R_0805_2012Metric,"1%,0805,0.125W",
C29,1,10nF,Hub:C_0805_2012Metric,"X7R,16V; evaluate DC-bias effective capacitance",
C30,1,4.7uF,Hub:C_0805_2012Metric,"X7R,16V; evaluate DC-bias effective capacitance",
Y2,1,ABM8-25.000MHZ-B2-T,Hub:Crystal_SMD_3225-4Pin_3.2x2.5mm,"25MHz,18pF load,<=50ppm total; verify crystal ordering specification.",
R30,1,1M,Hub:R_0805_2012Metric,"1%,0805,0.125W",
C31,1,18pF,Hub:C_0805_2012Metric,"C0G,50V",
C32,1,18pF,Hub:C_0805_2012Metric,"C0G,50V",
R31,1,49.9,Hub:R_0805_2012Metric,"1%,0805,0.125W",
R32,1,49.9,Hub:R_0805_2012Metric,"1%,0805,0.125W",
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
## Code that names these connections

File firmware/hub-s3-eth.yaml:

# Waveshare ESP32-S3-ETH-M, ESP32-S3R8 / 16MB flash.
# No camera, microSD card, or expansion board may be fitted: their pins are reused.
substitutions:
  node_name: ha-radio-hub-sensors
  friendly_name: HA Radio Hub Sensors
  bme680_address: "0x77"

esphome:
  name: ${node_name}
  friendly_name: ${friendly_name}
  min_version: 2026.10.2
  compile_process_limit: 2

esp32:
  board: esp32-s3-devkitc-1
  flash_size: 16MB
  framework:
    type: esp-idf

# Official ESPHome Waveshare ESP32-S3-ETH pin mapping.
ethernet:
  type: W5500
  clk_pin: GPIO13
  mosi_pin: GPIO11
  miso_pin: GPIO12
  cs_pin: GPIO14
  interrupt_pin: GPIO10
  reset_pin: GPIO9
  clock_speed: 20MHz

logger:
  level: INFO
  baud_rate: 0

api:
  encryption:
    key: !secret api_encryption_key
  reboot_timeout: 0s

ota:
  - platform: esphome
    password: !secret ota_password

esp32_ble_tracker:

bluetooth_proxy:
  active: true
  connection_slots: 3

uart:
  - id: zwave_uart
    tx_pin: GPIO17
    rx_pin: GPIO18
    baud_rate: 115200
    rx_buffer_size: 1024
    parity: NONE
    stop_bits: 1
  - id: radar_uart
    tx_pin: GPIO4
    rx_pin: GPIO5
    baud_rate: 256000
    rx_buffer_size: 1024
    parity: NONE
    stop_bits: 1

zwave_proxy:
  id: zwave_radio
  uart_id: zwave_uart

ld2450:
  id: radar
  uart_id: radar_uart

i2c:
  id: expansion_bus
  sda: GPIO1
  scl: GPIO2
  scan: true
  frequency: 100kHz

packages:
  environment: !include packages/bme680.yaml
  radar_entities: !include packages/ld2450.yaml

sensor:
  - platform: uptime
    name: Uptime
    entity_category: diagnostic
    update_interval: 60s

text_sensor:
  - platform: version
    name: ESPHome Version
    entity_category: diagnostic
  - platform: ethernet_info
    ip_address:
      name: Ethernet IP
      entity_category: diagnostic

binary_sensor:
  - platform: status
    name: API Connected
    entity_category: diagnostic

button:
  - platform: restart
    name: Restart sensor controller
    entity_category: diagnostic
    disabled_by_default: true

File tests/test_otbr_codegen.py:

"""Verify custom OTBR requests the crypto removed by ESPHome's default trimming."""
import json
from pathlib import Path
import subprocess
import sys
import tempfile
import unittest

ROOT = Path(__file__).resolve().parents[1]


class OtbrCodegenTest(unittest.TestCase):
    def test_thread_crypto_and_dtls_server_are_not_trimmed(self):
        with tempfile.TemporaryDirectory(prefix="otbr-codegen-") as directory:
            root = Path(directory)
            server = root / "server"
            server.mkdir()
            (server / "CMakeLists.txt").write_text("idf_component_register()\n")
            config = root / "fixture.yaml"
            config.write_text(f"""esphome:
  name: otbr-crypto-fixture
esp32:
  board: esp32-s3-devkitc-1
  framework:
    type: esp-idf
    version: 5.5.5
psram:
  mode: octal
ethernet:
  type: W5500
  clk_pin: GPIO13
  mosi_pin: GPIO11
  miso_pin: GPIO12
  cs_pin: GPIO14
  interrupt_pin: GPIO10
  reset_pin: GPIO9
network:
  enable_ipv6: true
uart:
  tx_pin: GPIO39
  rx_pin: GPIO40
  baud_rate: 256000
external_components:
  - source:
      type: local
      path: {json.dumps(str(ROOT / 'firmware/low-power/components'))}
    components: [low_power_otbr]
low_power_otbr:
  server_component_path: {json.dumps(str(server))}
  tx_pin: GPIO17
  rx_pin: GPIO18
  reset_pin: GPIO47
  boot_pin: GPIO48
""")
            result = subprocess.run([sys.executable, "-m", "esphome", "compile", "--only-generate", str(config)],
                                    capture_output=True, text=True)
            self.assertEqual(result.returncode, 0, result.stdout + result.stderr)
            build = root / ".esphome/build/otbr-crypto-fixture"
            source = (build / "sdkconfig.otbr-crypto-fixture").read_text()
            options = dict(line.split("=", 1) for line in source.splitlines() if line.startswith("CONFIG_"))
            self.assertIn("# ESPHOME_IDF_VERSION=5.5.5\n", source)
            # Required features may retain IDF's enabled defaults. The actual
            # post-Kconfig values are also checked after every full CI build.
            for name in ("TLS_SERVER_AND_CLIENT", "ECP_C", "CCM_C", "ECDSA_DETERMINISTIC"):
                self.assertNotEqual(options.get("CONFIG_MBEDTLS_" + name), "n", name)
            self.assertNotEqual(options.get("CONFIG_MBEDTLS_TLS_CLIENT_ONLY"), "y")
            self.assertNotEqual(options.get("CONFIG_MBEDTLS_TLS_DISABLED"), "y")
            self.assertEqual(options["CONFIG_MBEDTLS_SSL_PROTO_DTLS"], "y")
            self.assertEqual(options["CONFIG_OPENTHREAD_COMMISSIONER"], "y")
            self.assertEqual(options["CONFIG_OPENTHREAD_JOINER"], "y")


if __name__ == "__main__":
    unittest.main()

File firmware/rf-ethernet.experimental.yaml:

# EXPERIMENTAL replacement host for the CC1101: a SECOND Waveshare S3-ETH-M.
# Not a drop-in replacement for rf-airbridge MQTT/API contracts.
# No microSD or camera. CC1101 needs separate GDO0 (TX) and GDO2 (RX) wires.
esphome:
  name: ha-radio-hub-rf-test
  friendly_name: HA Radio Hub RF Test
  min_version: 2026.9.1
  compile_process_limit: 2

esp32:
  board: esp32-s3-devkitc-1
  flash_size: 16MB
  framework:
    type: esp-idf

ethernet:
  type: W5500
  clk_pin: GPIO13
  mosi_pin: GPIO11
  miso_pin: GPIO12
  cs_pin: GPIO14
  interrupt_pin: GPIO10
  reset_pin: GPIO9
  clock_speed: 20MHz

logger:
  level: INFO
  baud_rate: 0

ota:
  - platform: esphome
    password: !secret ota_password

api:
  encryption:
    key: !secret api_encryption_key
  reboot_timeout: 0s
  actions:
    - action: send_rc_switch
      variables:
        code: string
        protocol: int
        repeats: int
      then:
        - if:
            condition:
              lambda: |-
                for (const char bit : code) {
                  if (bit != '0' && bit != '1') return false;
                }
                return !code.empty() && code.size() <= 64 &&
                  protocol >= 1 && protocol <= 8 && repeats >= 1 && repeats <= 10;
            then:
              - remote_transmitter.transmit_rc_switch_raw:
                  code: !lambda return code;
                  protocol: !lambda return esphome::remote_base::RC_SWITCH_PROTOCOLS[protocol];
                  repeat:
                    times: !lambda return repeats;
                    wait_time: 10ms

spi:
  id: cc1101_spi
  interface: spi3
  clk_pin: GPIO7
  mosi_pin: GPIO8
  miso_pin: GPIO6

cc1101:
  id: rf_radio
  spi_id: cc1101_spi
  cs_pin: GPIO15
  frequency: 433.92MHz

globals:
  - id: rf_transmitting
    type: bool
    restore_value: false
    initial_value: 'false'

remote_transmitter:
  id: rf_tx
  pin: GPIO4
  carrier_duty_percent: 100%
  non_blocking: true
  on_transmit:
    then:
      - lambda: id(rf_transmitting) = true;
      - cc1101.begin_tx: rf_radio
  on_complete:
    then:
      - cc1101.begin_rx: rf_radio
      - lambda: id(rf_transmitting) = false;

remote_receiver:
  id: rf_rx
  pin: GPIO5
  tolerance: 30%
  filter: 250us
  idle: 4ms
  dump:
    - rc_switch
    - dooya
  on_rc_switch:
    then:
      - if:
          condition:
            lambda: return !id(rf_transmitting);
          then:
            - homeassistant.event:
                event: esphome.radio_hub_rf_received
                data:
                  protocol: !lambda return std::to_string(x.protocol);
                  code_decimal: !lambda return std::to_string(x.code);

sensor:
  - platform: uptime
    name: Uptime
    entity_category: diagnostic

binary_sensor:
  - platform: status
    name: API Connected
    entity_category: diagnostic
